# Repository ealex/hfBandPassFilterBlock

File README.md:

# hfBandPassFilterBlock
HF triple tuned band pass filter block

The filter coeficients are computed with https://rf-tools.com/lc-filter/

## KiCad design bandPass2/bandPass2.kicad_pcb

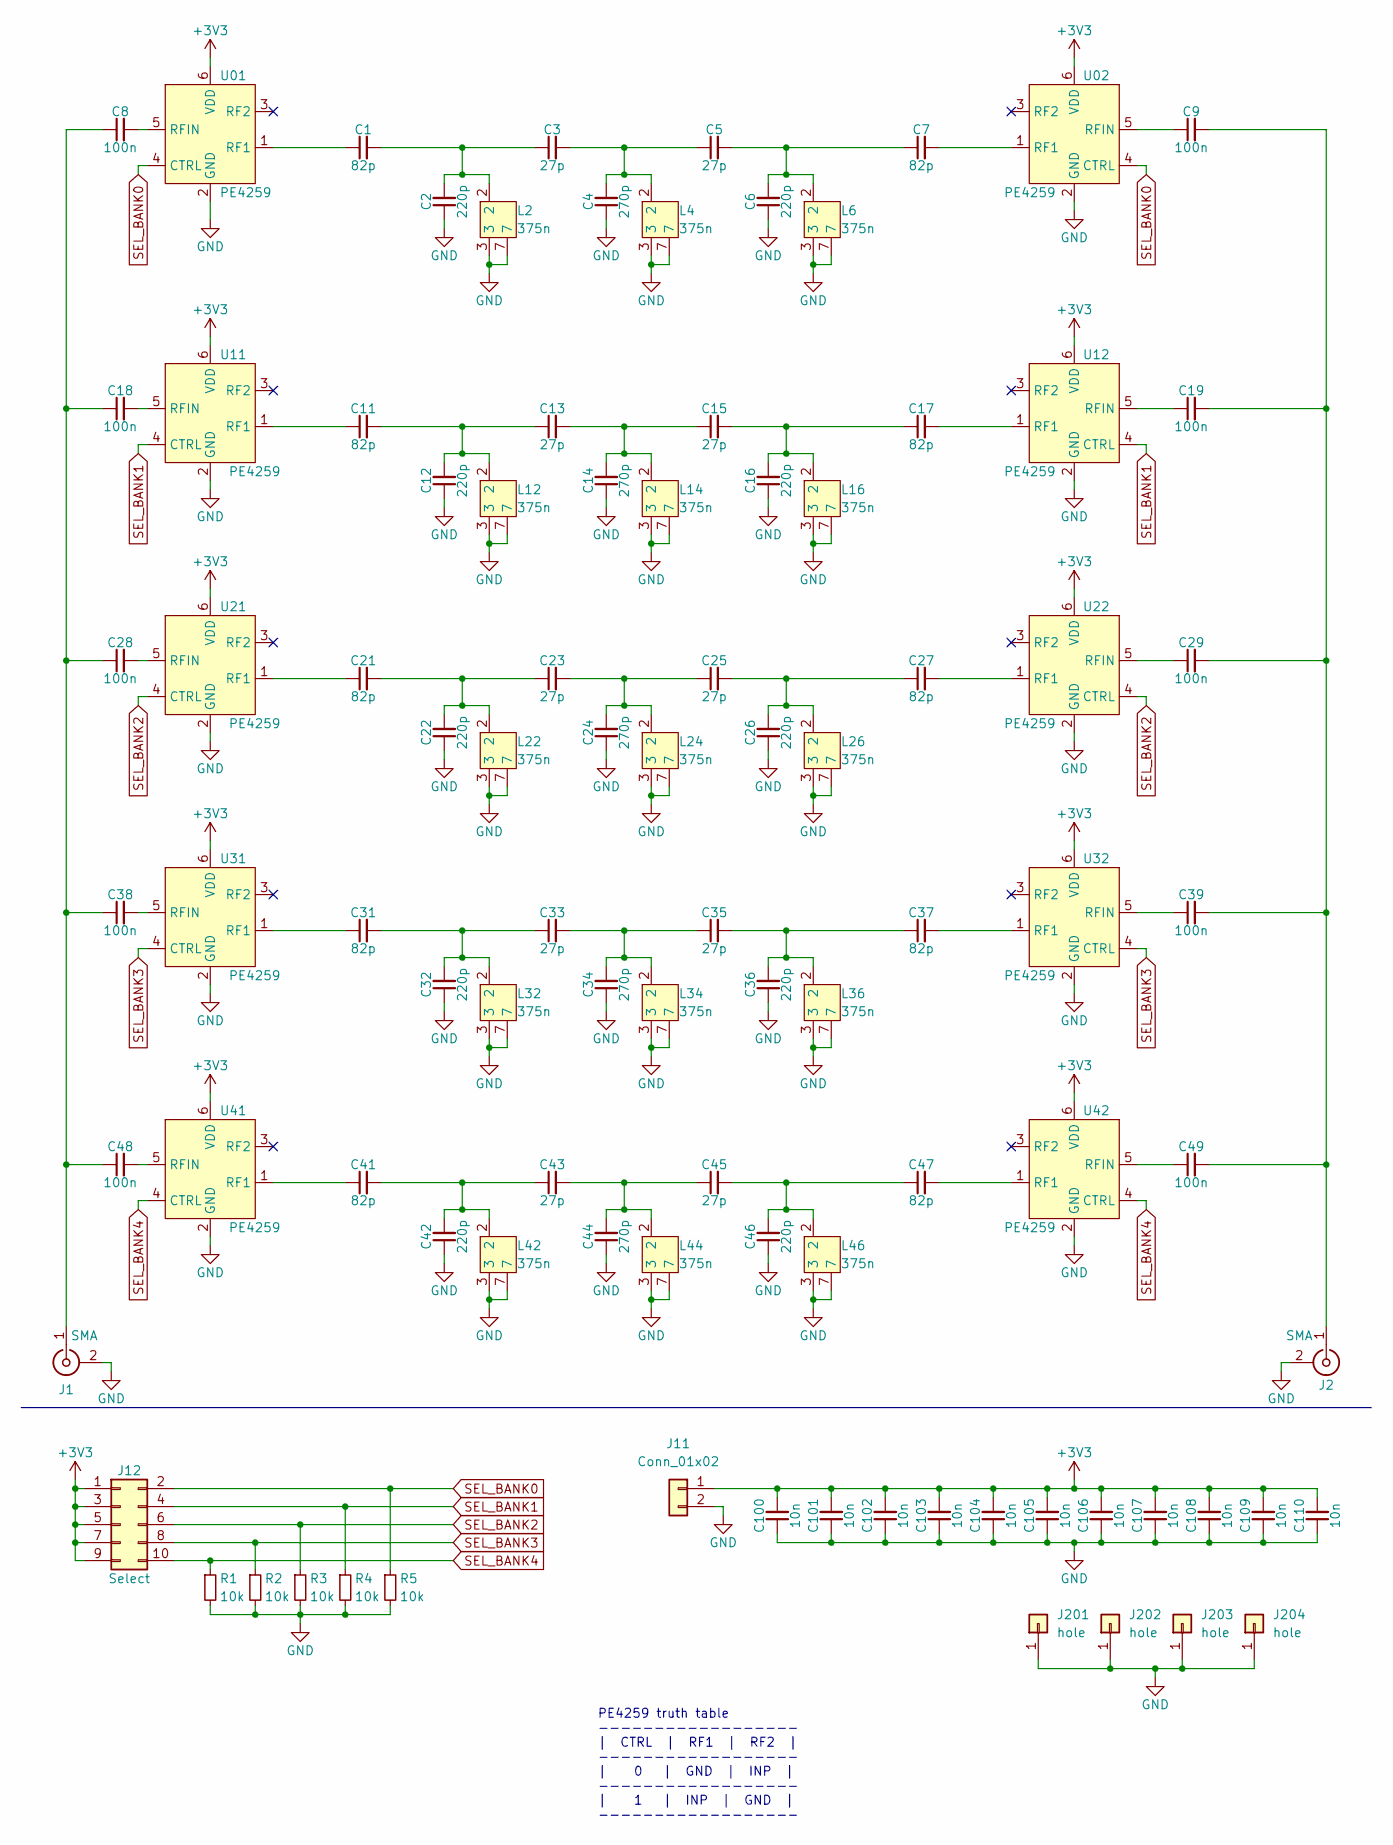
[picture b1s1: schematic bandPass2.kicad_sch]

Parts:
C1, C7, C11, C17, C21, C27, C31, C37, C41, C47: 82p; C_0805_2012Metric
C2, C6, C12, C16, C22, C26, C32, C36, C42, C46: 220p; C_0805_2012Metric
C3, C5, C13, C15, C23, C25, C33, C35, C43, C45: 27p; C_0805_2012Metric
C4, C14, C24, C34, C44: 270p; C_0805_2012Metric
C8, C9, C18, C19, C28, C29, C38, C39, C48, C49: 100n; C_0805_2012Metric
C100, C101, C102, C103, C104, C105, C106, C107, C108, C109, C110: 10n; C_0805_2012Metric
J1, J2: SMA
J11: Conn_01x02; PinHeader_1x02_P2.54mm_Vertical
J12: Select; PinHeader_2x05_P2.54mm_Vertical
J201, J202, J203, J204: hole; MountingHole_3.2mm_M3_DIN965_Pad
L2, L4, L6, L12, L14, L16, L22, L24, L26, L32, L34, L36, L42, L44, L46: 375n; TOKO_10K
R1, R2, R3, R4, R5: 10k; R_0805_2012Metric
U01, U02, U11, U12, U21, U22, U31, U32, U41, U42: PE4259; SOT-363_SC-70-6

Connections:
+3V3: C100.2, C101.2, C102.2, C103.2, C104.2, C105.2, C106.2, C107.2, C108.2, C109.2, C110.2, J11.1, J12.1, J12.3, J12.5, J12.7, J12.9, U01.6 (VDD), U02.6 (VDD), U11.6 (VDD), U12.6 (VDD), U21.6 (VDD), U22.6 (VDD), U31.6 (VDD), U32.6 (VDD), U41.6 (VDD), U42.6 (VDD)
GND: C2.1, C4.1, C6.1, C12.1, C14.1, C16.1, C22.1, C24.1, C26.1, C32.1, C34.1, C36.1, C42.1, C44.1, C46.1, C100.1, C101.1, C102.1, C103.1, C104.1, C105.1, C106.1, C107.1, C108.1, C109.1, C110.1, J1.2 (Ext), J2.2 (Ext), J11.2, J201.1, J202.1, J203.1, J204.1, L2.3, L2.7, L4.3, L4.7, L6.3, L6.7, L12.3, L12.7, L14.3, L14.7, L16.3, L16.7, L22.3, L22.7, L24.3, L24.7, L26.3, L26.7, L32.3, L32.7, L34.3, L34.7, L36.3, L36.7, L42.3, L42.7, L44.3, L44.7, L46.3, L46.7, R1.2, R2.2, R3.2, R4.2, R5.2, U01.2 (GND), U02.2 (GND), U11.2 (GND), U12.2 (GND), U21.2 (GND), U22.2 (GND), U31.2 (GND), U32.2 (GND), U41.2 (GND), U42.2 (GND)
unnamed: C1.1, U01.1 (RF1)
unnamed: C1.2, C2.2, C3.1, L2.2
unnamed: C3.2, C4.2, C5.1, L4.2
unnamed: C5.2, C6.2, C7.1, L6.2
unnamed: C7.2, U02.1 (RF1)
unnamed: C8.2, U01.5 (RFIN)
unnamed: C9.1, U02.5 (RFIN)
unnamed: C11.1, U11.1 (RF1)
unnamed: C11.2, C12.2, C13.1, L12.2
unnamed: C13.2, C14.2, C15.1, L14.2
unnamed: C15.2, C16.2, C17.1, L16.2
unnamed: C17.2, U12.1 (RF1)
unnamed: C8.1, C18.1, C28.1, C38.1, C48.1, J1.1 (In)
unnamed: C18.2, U11.5 (RFIN)
unnamed: C19.1, U12.5 (RFIN)
unnamed: C9.2, C19.2, C29.2, C39.2, C49.2, J2.1 (In)
unnamed: C21.1, U21.1 (RF1)
unnamed: C21.2, C22.2, C23.1, L22.2
unnamed: C23.2, C24.2, C25.1, L24.2
unnamed: C25.2, C26.2, C27.1, L26.2
unnamed: C27.2, U22.1 (RF1)
unnamed: C28.2, U21.5 (RFIN)
unnamed: C29.1, U22.5 (RFIN)
unnamed: C31.1, U31.1 (RF1)
unnamed: C31.2, C32.2, C33.1, L32.2
unnamed: C33.2, C34.2, C35.1, L34.2
unnamed: C35.2, C36.2, C37.1, L36.2
unnamed: C37.2, U32.1 (RF1)
unnamed: C38.2, U31.5 (RFIN)
unnamed: C39.1, U32.5 (RFIN)
unnamed: C41.1, U41.1 (RF1)
unnamed: C41.2, C42.2, C43.1, L42.2
unnamed: C43.2, C44.2, C45.1, L44.2
unnamed: C45.2, C46.2, C47.1, L46.2
unnamed: C47.2, U42.1 (RF1)
unnamed: C48.2, U41.5 (RFIN)
unnamed: C49.1, U42.5 (RFIN)
SEL_BANK0: J12.2, R5.1, U01.4 (CTRL), U02.4 (CTRL)
SEL_BANK1: J12.4, R4.1, U11.4 (CTRL), U12.4 (CTRL)
SEL_BANK2: J12.6, R3.1, U21.4 (CTRL), U22.4 (CTRL)
SEL_BANK3: J12.8, R2.1, U31.4 (CTRL), U32.4 (CTRL)
SEL_BANK4: J12.10, R1.1, U41.4 (CTRL), U42.4 (CTRL)

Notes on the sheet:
PE4259 truth table ------------------ | CTRL | RF1 | RF2 | ------------------ | 0 | GND | INP | ------------------ | 1 | INP | GND | ------------------

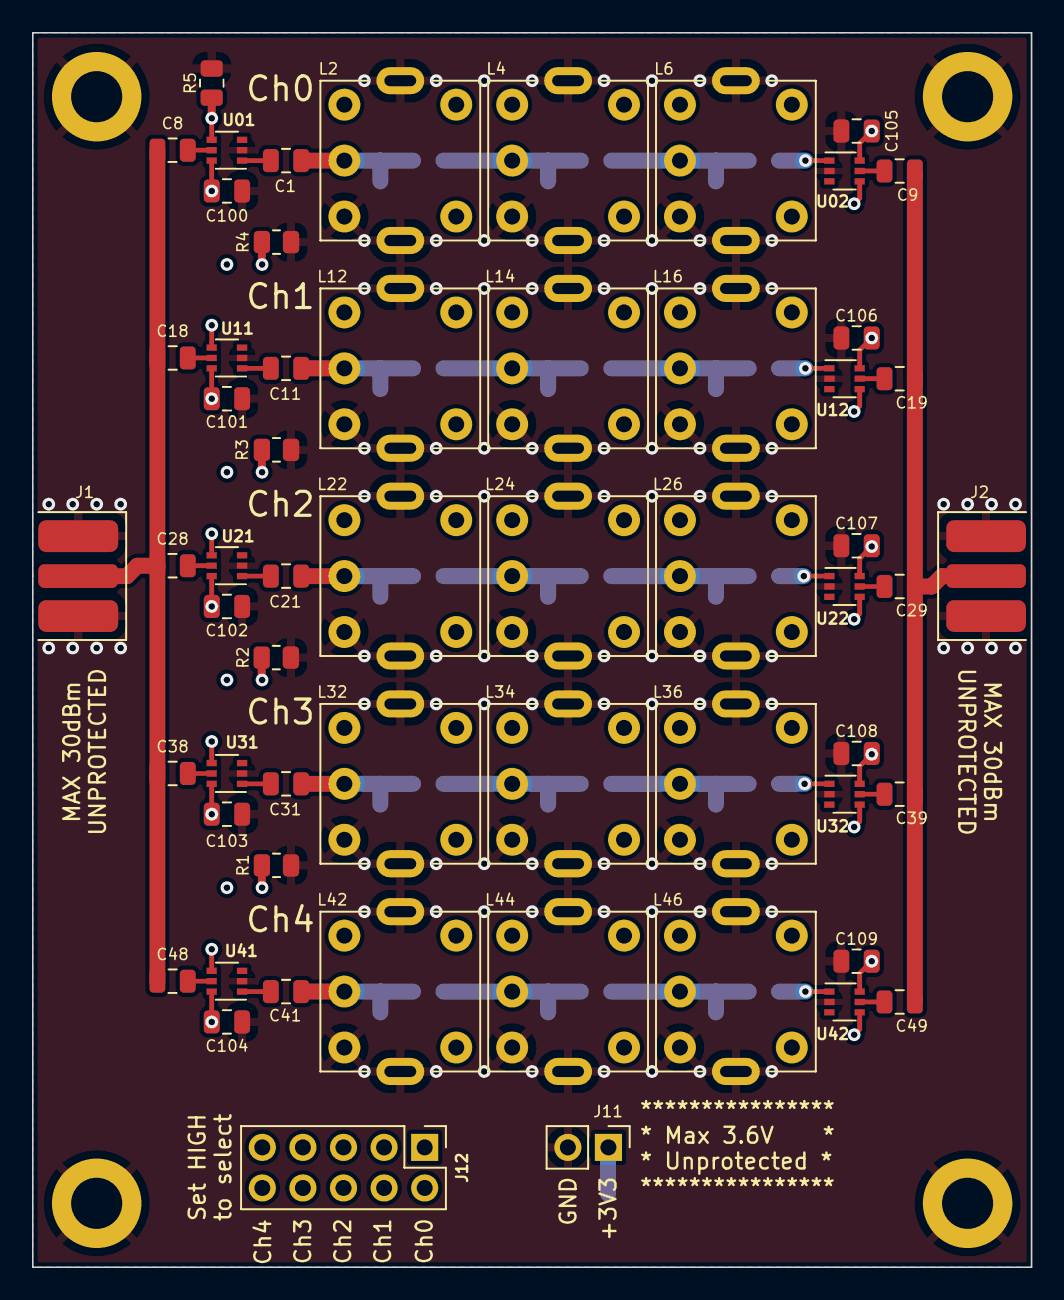
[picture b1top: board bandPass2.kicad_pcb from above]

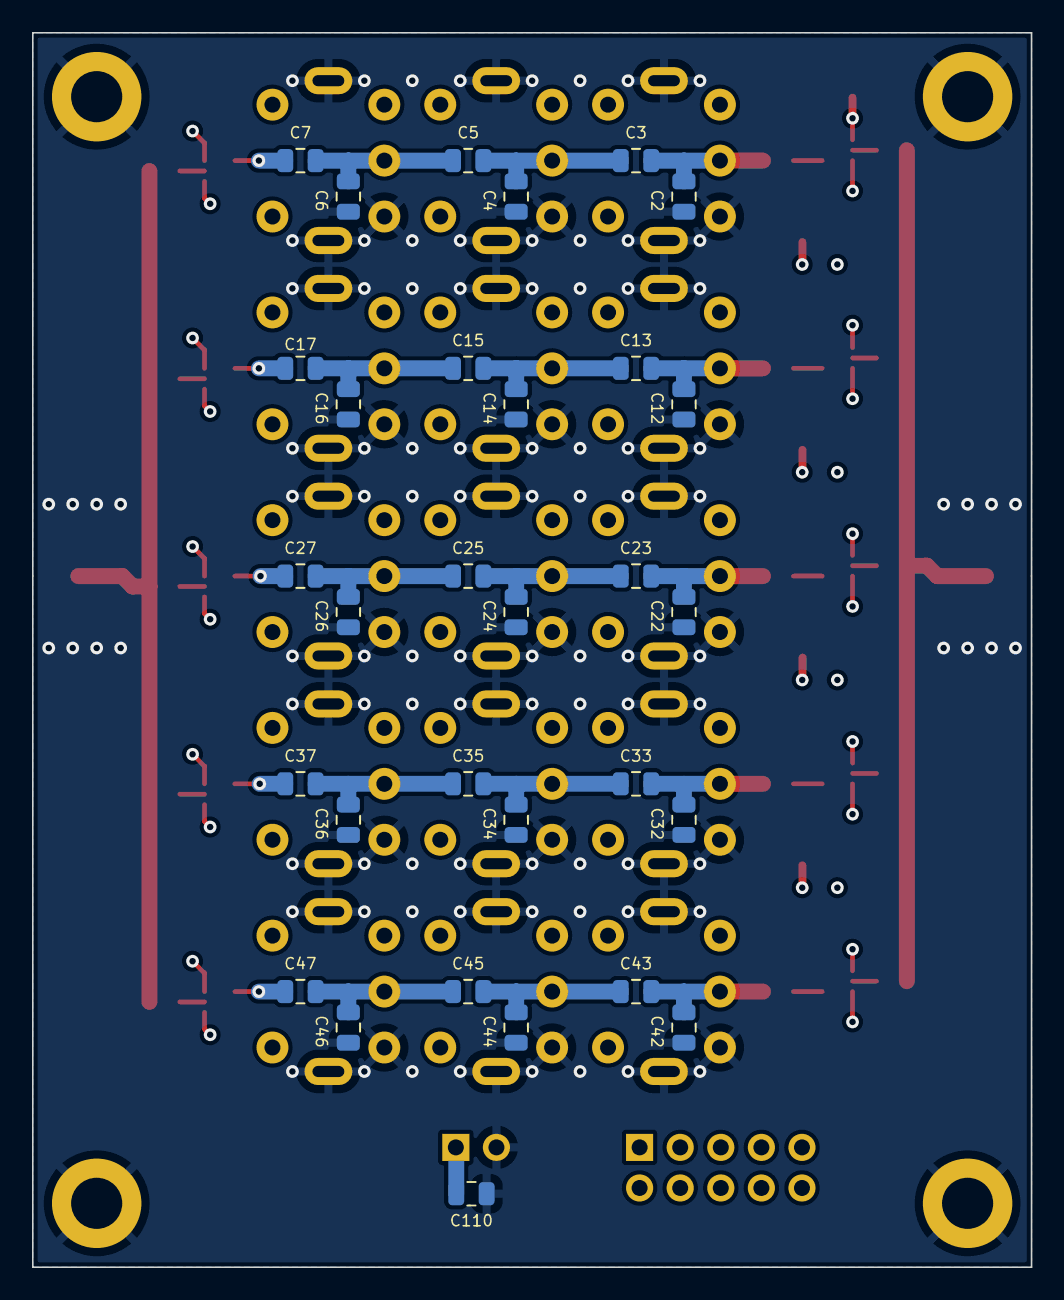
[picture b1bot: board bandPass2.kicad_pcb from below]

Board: 4 copper layers, 62.5 x 77.2 mm, 94 parts (31 on the bottom side), 44 nets.

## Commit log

2023-08-31 add RF switch and filter coil
2023-08-31 filter coeficients file
2023-08-31 add schematic
2023-08-31 add pdf schematic
2023-08-31 pcb clean-up
2023-08-31 clean-up, add pcb render
2023-08-31 add bom
2023-11-07 add PE4259 switch
2023-11-07 Add TOKO 10K 3d model
2023-11-07 update schematic and pcb
2023-11-07 regenerate pdf
2024-01-09 start defining filter banks
2024-01-11 add new filters
2024-02-06 add last filter
